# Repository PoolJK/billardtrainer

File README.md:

# Billardtrainer
A snooker and pool training system in development with Python on Raspberry-Pi and Android.

Using libraries (Win 10):  
```
Python 3.7.3
OpenCV (opencv-python & -contrib) 4.1.0.25
Imutils (imutils) 0.5.2
PyBluez (pybluez) 0.22
Numpy 1.16.3
GitPython 2.1.11
```

on Raspberry-Pi:  
```
PiCamera
opencv-python
opencv-python-contrib
imutils
numpy

und noch anderes Zeug... mal checken was gebraucht wird, um den Pi neu aufzusetzen
```

Ist das noch relevant?:  
Make sure to add `billardtrainer (/software)` as your
src root folder in pycharm to prevent 'unresolved reference'-error.

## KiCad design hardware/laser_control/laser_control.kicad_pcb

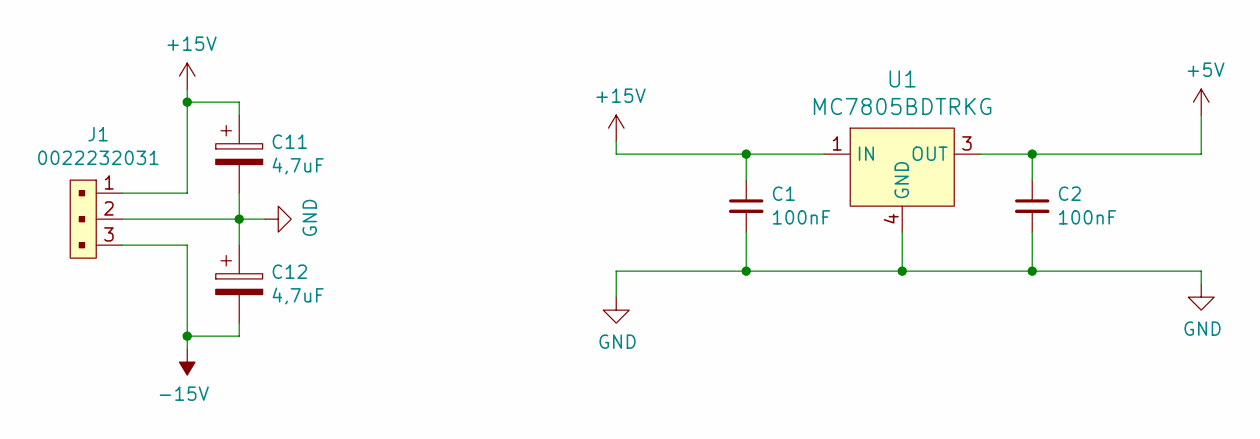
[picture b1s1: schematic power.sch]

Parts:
C1, C2: 100nF; C_0805_2012Metric_Pad1.15x1.40mm_HandSolder
C11, C12: 4,7uF; C_1210_3225Metric_Pad1.42x2.65mm_HandSolder
J1: 0022232031; PinHeader_1x3_P2.54mm_Drill1.02mm; MPN 0022232031; Digi-Key_PN WM4201-ND
U1: MC7805BDTRKG; TO-252-3; MPN MC7805BDTRKG; Digi-Key_PN MC7805BDTRKGOSCT-ND

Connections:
+5V: C2.1, U1.3 (OUT); also elsewhere on the board
+15V: C1.1, C11.1, J1.1, U1.1 (IN); also elsewhere on the board
-15V: C12.2, J1.3; also elsewhere on the board
GND: C1.2, C2.2, C11.2, C12.1, J1.2, U1.4 (GND); also elsewhere on the board

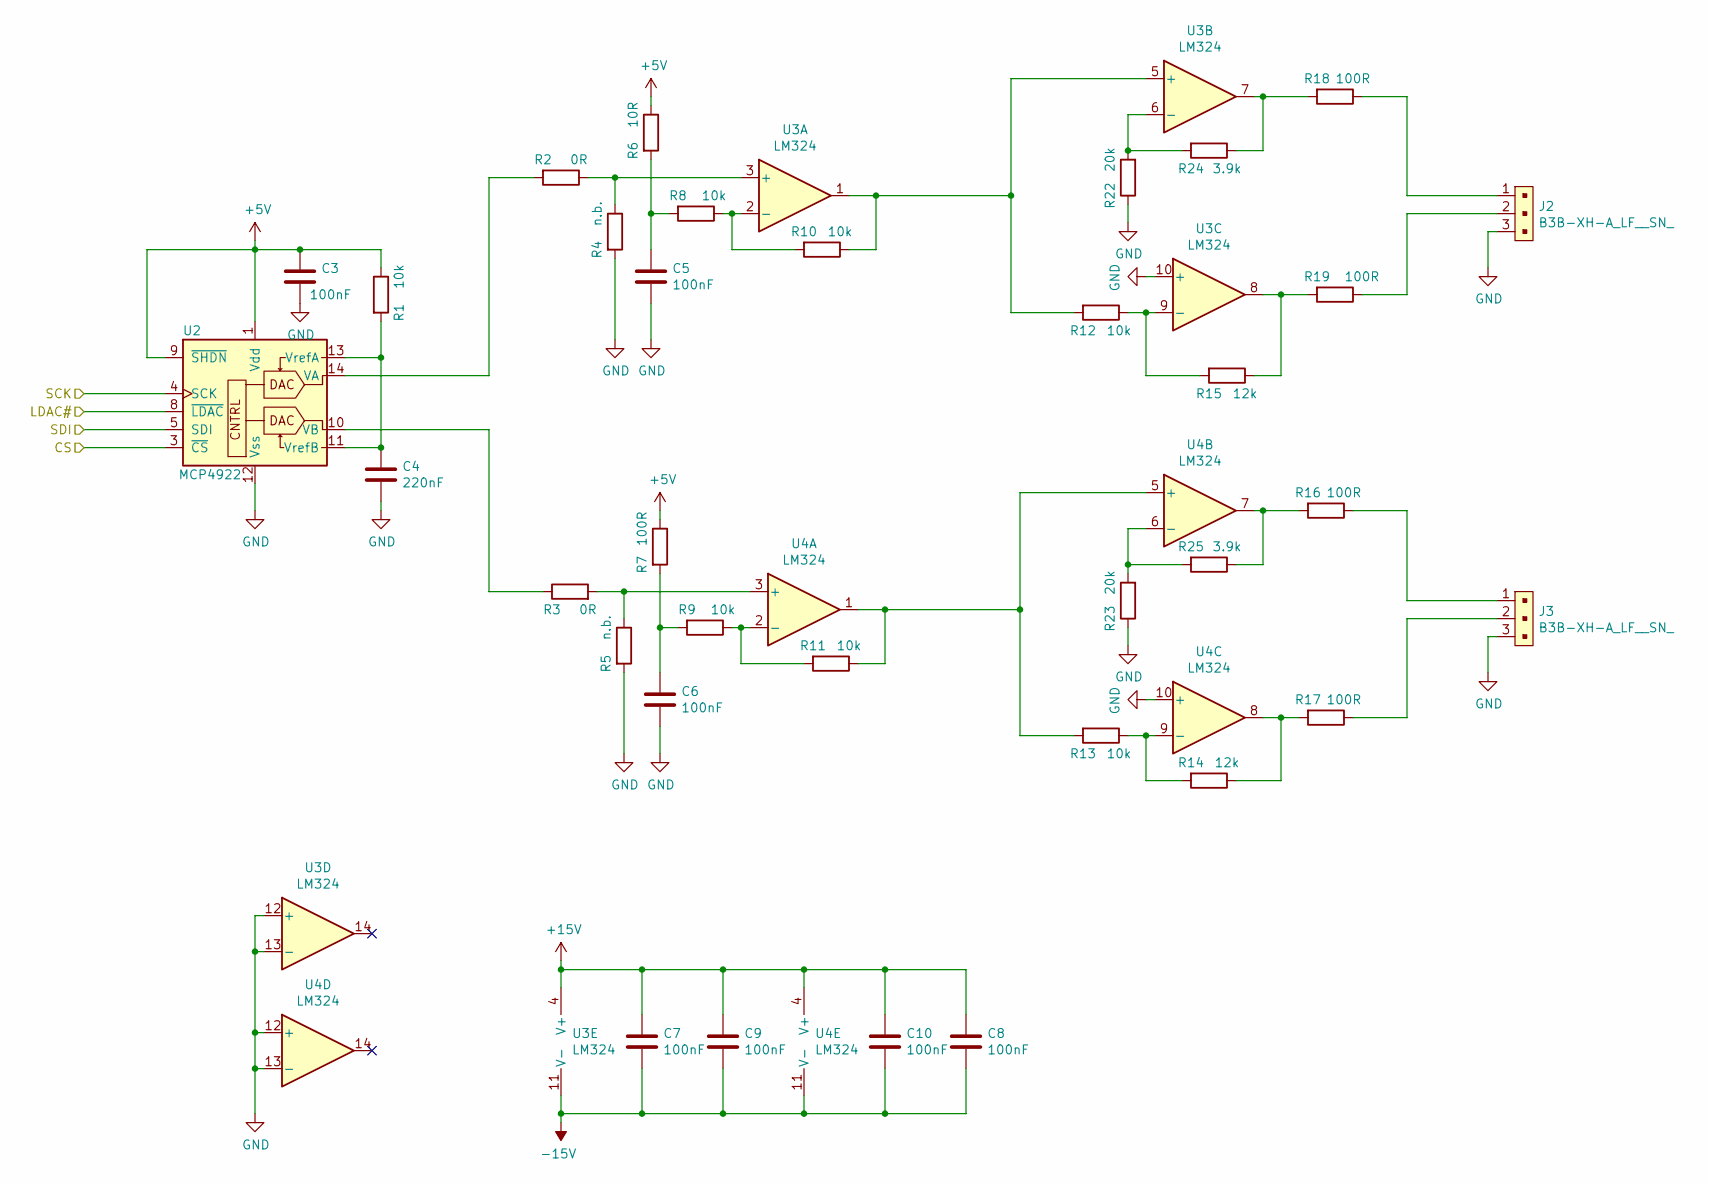
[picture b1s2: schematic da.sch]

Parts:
C3, C5, C6, C7, C8, C9, C10: 100nF; C_0805_2012Metric_Pad1.15x1.40mm_HandSolder
C4: 220nF; C_0805_2012Metric_Pad1.15x1.40mm_HandSolder
J2, J3: B3B-XH-A_LF__SN_; PinHeader_1x3_P2.5mm_Drill1.1mm; MPN B3B-XH-A(LF)(SN); Digi-Key_PN 455-2248-ND
R1, R8, R9, R10, R11, R12, R13: 10k; R_0805_2012Metric_Pad1.15x1.40mm_HandSolder
R2, R3: 0R; R_0805_2012Metric_Pad1.15x1.40mm_HandSolder
R4, R5: n.b.; R_0805_2012Metric_Pad1.15x1.40mm_HandSolder
R6: 10R; R_0805_2012Metric_Pad1.15x1.40mm_HandSolder
R7, R16, R17, R18, R19: 100R; R_0805_2012Metric_Pad1.15x1.40mm_HandSolder
R14, R15: 12k; R_0805_2012Metric_Pad1.15x1.40mm_HandSolder
R22, R23: 20k; R_0805_2012Metric_Pad1.15x1.40mm_HandSolder
R24, R25: 3.9k; R_0805_2012Metric_Pad1.15x1.40mm_HandSolder
U2: MCP4922; TSSOP-14_4.4x5mm_P0.65mm
U3, U4: LM324; SOIC-14_3.9x8.7mm_P1.27mm

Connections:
+5V: C3.1, R1.1, R6.1, R7.1, U2.1 (Vdd), U2.9 (~SHDN); also elsewhere on the board
+15V: C7.1, C8.1, C9.1, C10.1, U3.4 (V+), U4.4 (V+); also elsewhere on the board
-15V: C7.2, C8.2, C9.2, C10.2, U3.11 (V-), U4.11 (V-); also elsewhere on the board
/DAC/CS: U2.3 (~CS); also elsewhere on the board
/DAC/LDAC#: U2.8 (~LDAC); also elsewhere on the board
/DAC/SCK: U2.4 (SCK); also elsewhere on the board
/DAC/SDI: U2.5 (SDI); also elsewhere on the board
GND: C3.2, C4.2, C5.2, C6.2, J2.3, J3.3, R4.2, R5.2, R22.1, R23.1, U2.12 (Vss), U3.10 (+), U3.12 (+), U3.13 (-), U4.10 (+), U4.12 (+), U4.13 (-); also elsewhere on the board
unnamed: C4.1, R1.2, U2.11 (VrefB), U2.13 (VrefA)
unnamed: C5.1, R6.2, R8.2
unnamed: C6.1, R7.2, R9.2
unnamed: J2.1, R18.1
unnamed: J2.2, R19.1
unnamed: J3.1, R16.1
unnamed: J3.2, R17.1
unnamed: R2.1, R4.1, U3.3 (+)
unnamed: R2.2, U2.14 (VA)
unnamed: R3.1, U2.10 (VB)
unnamed: R3.2, R5.1, U4.3 (+)
unnamed: R10.1, R12.2, U3.1, U3.5 (+)
unnamed: R8.1, R10.2, U3.2 (-)
unnamed: R11.1, R13.2, U4.1, U4.5 (+)
unnamed: R9.1, R11.2, U4.2 (-)
unnamed: R12.1, R15.2, U3.9 (-)
unnamed: R13.1, R14.2, U4.9 (-)
unnamed: R14.1, R17.2, U4.8
unnamed: R15.1, R19.2, U3.8
unnamed: R16.2, R25.1, U4.7
unnamed: R18.2, R24.1, U3.7
unnamed: R22.2, R24.2, U3.6 (-)
unnamed: R23.2, R25.2, U4.6 (-)

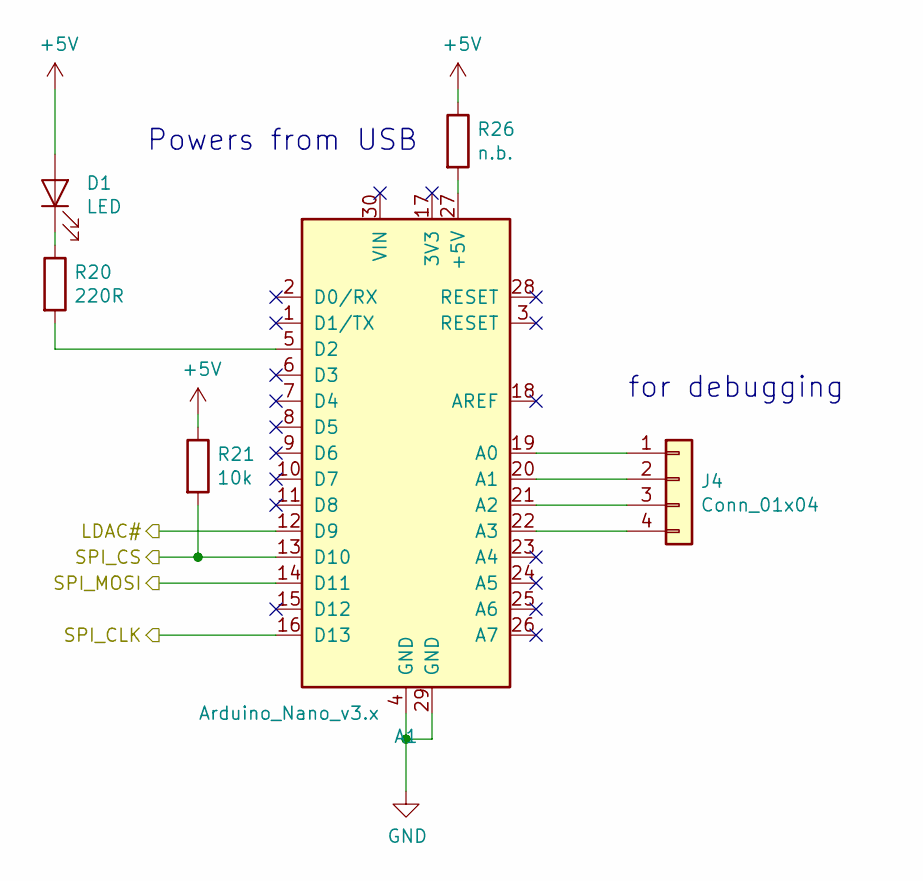
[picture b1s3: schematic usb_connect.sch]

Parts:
A1: Arduino_Nano_v3.x; Arduino_Nano
D1: LED; LED_3mm_Radial
J4: Conn_01x04; PinHeader_1x04_P2.54mm_Vertical
R20: 220R; R_0805_2012Metric_Pad1.15x1.40mm_HandSolder
R21: 10k; R_0805_2012Metric_Pad1.15x1.40mm_HandSolder
R26: n.b.; R_0805_2012Metric_Pad1.15x1.40mm_HandSolder

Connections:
+5V: D1.2 (A), R21.1, R26.1; also elsewhere on the board
/DAC/CS: A1.13 (D10), R21.2; also elsewhere on the board
/DAC/LDAC#: A1.12 (D9); also elsewhere on the board
/DAC/SCK: A1.16 (D13); also elsewhere on the board
/DAC/SDI: A1.14 (D11); also elsewhere on the board
GND: A1.4 (GND), A1.29 (GND); also elsewhere on the board
unnamed: A1.5 (D2), R20.2
unnamed: A1.19 (A0), J4.1
unnamed: A1.20 (A1), J4.2
unnamed: A1.21 (A2), J4.3
unnamed: A1.22 (A3), J4.4
unnamed: A1.27 (+5V), R26.2
unnamed: D1.1 (K), R20.1

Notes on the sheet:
Powers from USB
for debugging

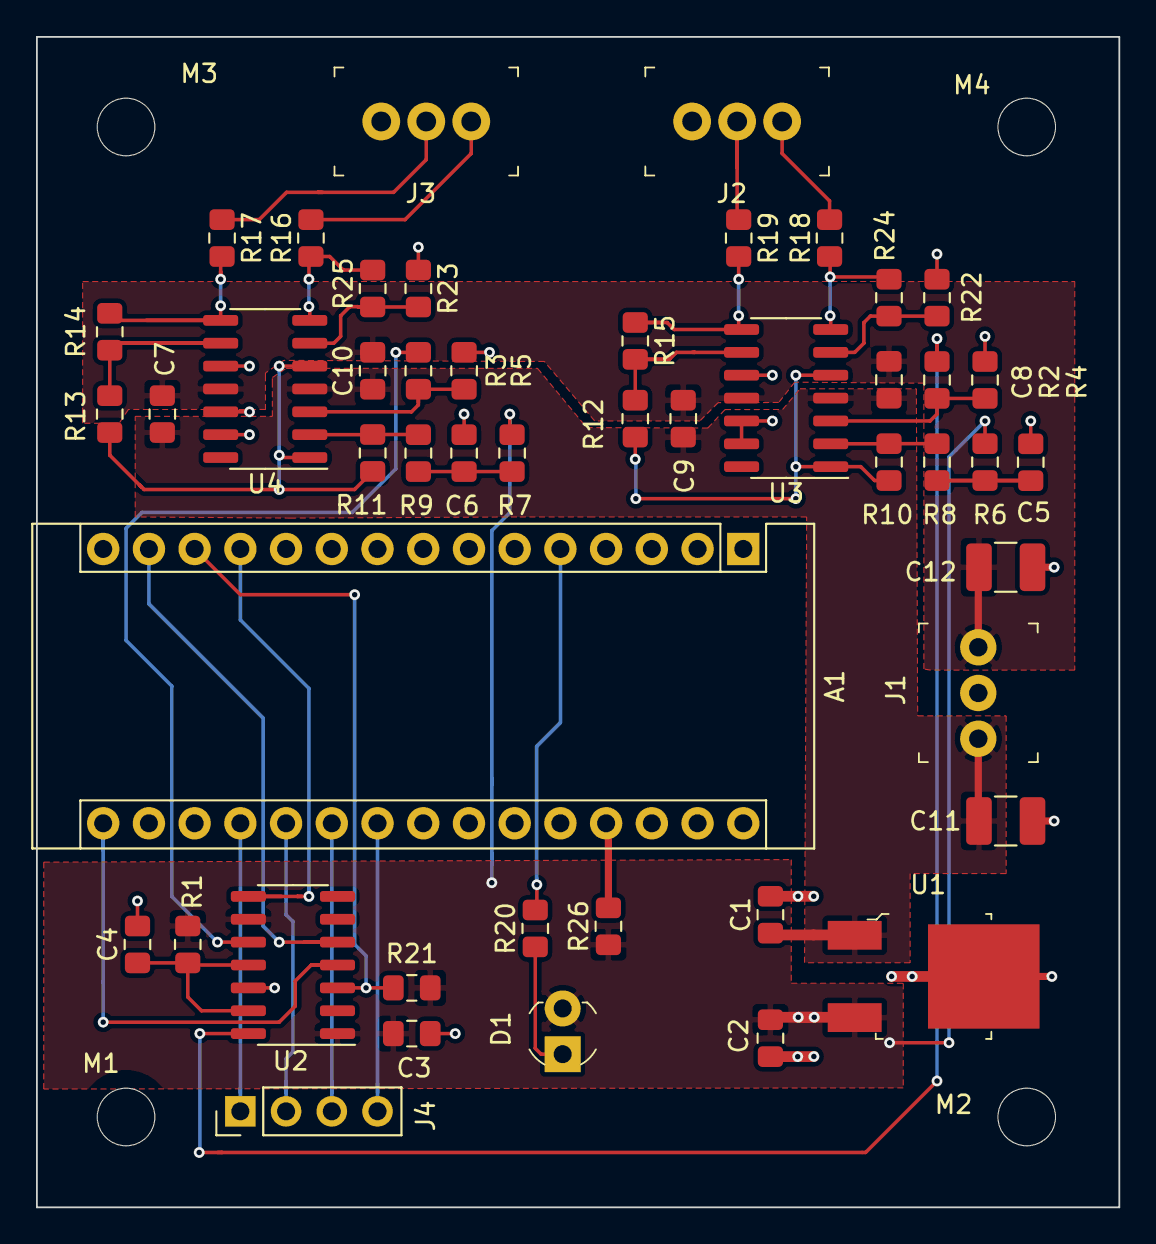
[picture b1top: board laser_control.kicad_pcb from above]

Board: 2 copper layers, 60.1 x 65.0 mm, 52 parts (0 on the bottom side), 38 nets.

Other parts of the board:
M1, M2, M3, M4: MountingHole_3.2mm_M3

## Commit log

2019-03-23 nur um directory anzulegen
2019-03-24 even more directories
2019-03-26 first software
2019-03-26 added some test images
2019-03-28 files added before new checkout
2019-04-02 detecting of local images works
2019-04-03 Vorschlag zur Struktur während der frühen Entwicklungsphase. Würder mich interessieren, ob das bei euch läuft, vor allem, ob der pi das schluckt, ich hatte Schwierigkeiten mit den imports. Bei mir fu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
2019-04-04 new settings file for storing global settings variables first working beamer class for warping image
2019-04-05 hier schonmal zwei der Bilder
    der Rest folgt, sobald mein Handy wieder Strom hat
2019-04-06 added new testimages and android folder
2019-04-09 detection of snooker balls using hsv colorspace and houghcircles v2
2019-04-09 changed command order to work on raspy
2019-04-09 different command on raspy
2019-04-10 subtracting background from video file with moving balls on it
2019-04-11 Details siehe readme.md Ablauf und Struktur angepasst
2019-04-11 new camera test for adjusting, new subdirectory for tools etc
2019-04-11 dev-grind
2019-04-11 fixed file structure
2019-04-11 after merge cleanup main.py runs billardtrainer.py runs
2019-04-12 updated run configurations added link to rebase/merge explanation
2019-04-12 testing with the new set of images
    added runconfiguration with calibration files and src
    added standard image size in camera for debugging
2019-04-13 Update links.md
    Links to better got usage
2019-04-13 camera datasheet aded
2019-04-14 added push to pi and run; added debug output in camera and detect_test; updated readmes; added new images
2019-04-14 added new link and git cheatsheet
2019-04-14 added different calibration method restructured camera to allow developing calibration separate from process
2019-04-15 added fisheye calibration to camera.py as `method2`
2019-04-15 added argparse-argument for display and source resolutions; added check if on pi to main script;
2019-04-15 correction hinzugefügt
2019-04-16 added trackbars and formatted code to run in loop
2019-04-16 test commit in test branch
2019-04-16 camera saves images during interactive calibration else camera reads calibration files with number placeholder; see added runconfiguration
2019-04-17 added queued source reading for fps increase edited run configurations for pi upload working on error fix when opening capture again
2019-04-17 camera test with live image
2019-04-17 bug fixing the new queued camera still has bugs though
2019-04-17 finished bug fixing got stable stream from network and camera with decent fps
2019-04-18 added camera preview as argument added camera test for available resolutions (video) working on: change capture mode (YUV(max 10fps) or MJPG(max30fps) for my webcam) to further improve fps perhaps us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
2019-04-19 fixed imports, implemented beamer class, automated calibration, added yet another cmdline flag
2019-04-19 first try with dummy camera class and correction
2019-04-19 loading/saving calibration per device in file fixed InputStream to accept pictures again
2019-04-20 added: alternative calibration for non-fisheye camera;
2019-04-20 first working correction with mini table as reference
2019-04-20 first implementation of resolution correction
2019-04-20 trying temporal filter in InputStream
2019-04-22 beamer and visual_item with mm as unit new classes to be displayed on table
2019-04-22 preparing work on table homography
2019-04-23 file renamed for windows compability
2019-04-23 all items work on pc now
2019-04-23 tests added
2019-04-23 beamer test runs on raspy
2019-04-24 ran code inspection applied code fixes so program runs without fatal errors appended missing functions and parameters to visual_item classes made pic<>mm conversion consistent, not able to check if i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
2019-04-24 Rückschritte immer am Start, wat willze machen.. in this episode: Kalibrierung verschlimmbessert some codefixes, imports now same as in master
2019-04-27 Episode IV: A new program
2019-04-27 chapter 1: in a python terminal on a raspberry pi, far, far away
2019-05-04 crazy shit
2019-05-04 table simulation for testing on pc while we don't have camera and beamer set up
2019-05-04 bluetooth begins
2019-05-04 directory structure changed
2019-05-04 chapter 1: in a python terminal on a raspberry pi, far, far away (#4)
    * chapter 1: in a python terminal on a raspberry pi, far, far away
    * directory structure changed
2019-05-04 updated readme and links
2019-05-16 added android code from SnooPhy project
    updated readme and links
2019-05-16 adding bluetooth to ui
2019-05-18 Adding Bluetooth functionality
2019-05-22 returning to work on beamer and camera setup
2019-05-22 adding lines
2019-05-22 adding ghost
2019-05-22 small fixes, code cleanup
2019-05-23 resuming physics calculations setup
2019-05-24 first implementation: contact rolling ball <-> still ball node structure is a bit too adhoc
2019-05-25 developing at the club with raspi9b
2019-05-25 eureka
2019-05-26 table_sim updated; some restructuring
2019-05-26 new day, new luck @the club
2019-05-27 developing @home: reading images again...
2019-05-27 threaded detection. to be tested soonish
2019-05-28 testing detection @club
2019-05-28 back @ the club pi sends detected balls to app, app sends calculated lines to pi pi displays all table sim simulates everything
2019-05-29 parallel threads speed is crazy fast
2019-05-29 club testing
2019-05-31 corrections
2019-06-04 reaching the speed limit
2019-06-04 added empty activity
2019-06-06 make things simpler again
2019-06-08 fixing calc and draw, added debug signing config
2019-06-08 moving the table display to customSurfaceView it's gonna be tough y'all
2019-06-09 created 'Drill' class fixed surfaceView and helper ball display in 'Main' some refactoring fixed missing bluetooth reply from table_sim
2019-06-09 made Drill a Fragment removed sim
2019-06-09 added build flavors
2019-06-10 removed unused activities, edited flavours added continuous detection mode
2020-02-19 first version of webserver support
2020-02-19 show result image in web page
2020-02-20 put websever in class
2020-02-21 webserver added
2020-02-24 changed imports (again) works with webserver thread
2020-02-25 added detector thread some relocation of settings
2020-03-12 drill page added
2020-03-13 added to lesson page
2020-03-20 some typos missing files
